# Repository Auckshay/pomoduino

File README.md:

# Pomoduino (An Arduino UNO shield)

A little DIY Pomodoro timer to keep you focused and away from pesky distractions.

(3D model)

## How it works
To use the pomoduino, in front of a distracting object, making sure that the sensor is unobscured, and a clear path in front of it to detect movement. Then set the timer length and break length, and start it.
## Why I made this
Every single time I sat down, planning to work on something, I always found myself instinctively reaching for my phone. I knew this was an issue, and I, of course, tried to set screen time limits and pomodoro timers to keep me locked in. Still, I found myself either disabling them or just finding some other convoluted workaround subconsciously. But I knew that I've always been a person who obeys physical obstruction. That's when I got the idea of creating a device that aided me in focus with a pomoduro timer, but also physically reminded me to focus up.
## Design Images
### Schematic Design

### PCB Design

## B.O.M.

|Name                                                                                                                  |Purpose                                   |Qty|Cost (USD)|LINK                                                                                  |Distributor|
|----------------------------------------------------------------------------------------------------------------------|------------------------------------------|---|----------|--------------------------------------------------------------------------------------|-----------|
|Monochrome_OLED_128X64_.96_I2C-1pc                                                                                    |Display Count Down, Distraction Notif, ect|1  |6.99$     |https://a.co/d/0dFfSqWY                                                               |Amazon     |
|2.54mm Pin Header, Male Straight Single Row Header Pin 180 Degree Connector,1x2 1x3 1x4 1x5 1x6 1x7 1x8 1x9 1x10 1x12 |For mounting to Arduino UNO               |1  |11.99$    |https://a.co/d/0gofrzR4                                                               |Amazon     |
|Passive Buzzer-5pc                                                                                                    |Auditory Output                           |1  |1.18$     |https://www.aliexpress.us/item/3256806074013807.html                                  |AliExpress |
|220Ω Resistor-10pc                                                                                                    |Current limiting                          |1  |1.46$     |https://www.aliexpress.us/item/3256802927431747.html                                  |AliExpress |
|Colorful Push Button-12mm-15pc                                                                                        |Human Interaction                         |1  |5.95$     |https://www.adafruit.com/product/1010                                                 |Adafruit   |
|HC-SR04-1pc                                                                                                           |Distance measurement                      |1  |6.17$     |https://www.aliexpress.us/item/3256810043926609.html?gatewayAdapt=glo2usa             |AliExpress |
|PCB-5pc                                                                                                               |For mounting and connecting all components|1  |5.00$     |https://www.pcbway.com/orderonline.aspx?outsideid=d9d46809-3d4a-4ff4-aac3-b91ac39b3b48|PCBWAY     |

### External Hardware Required
- 1x Arduino UNO (R3 or R4) – The host board.
- 1x USB-C Cable or USB-B, depending on the Arduino version.

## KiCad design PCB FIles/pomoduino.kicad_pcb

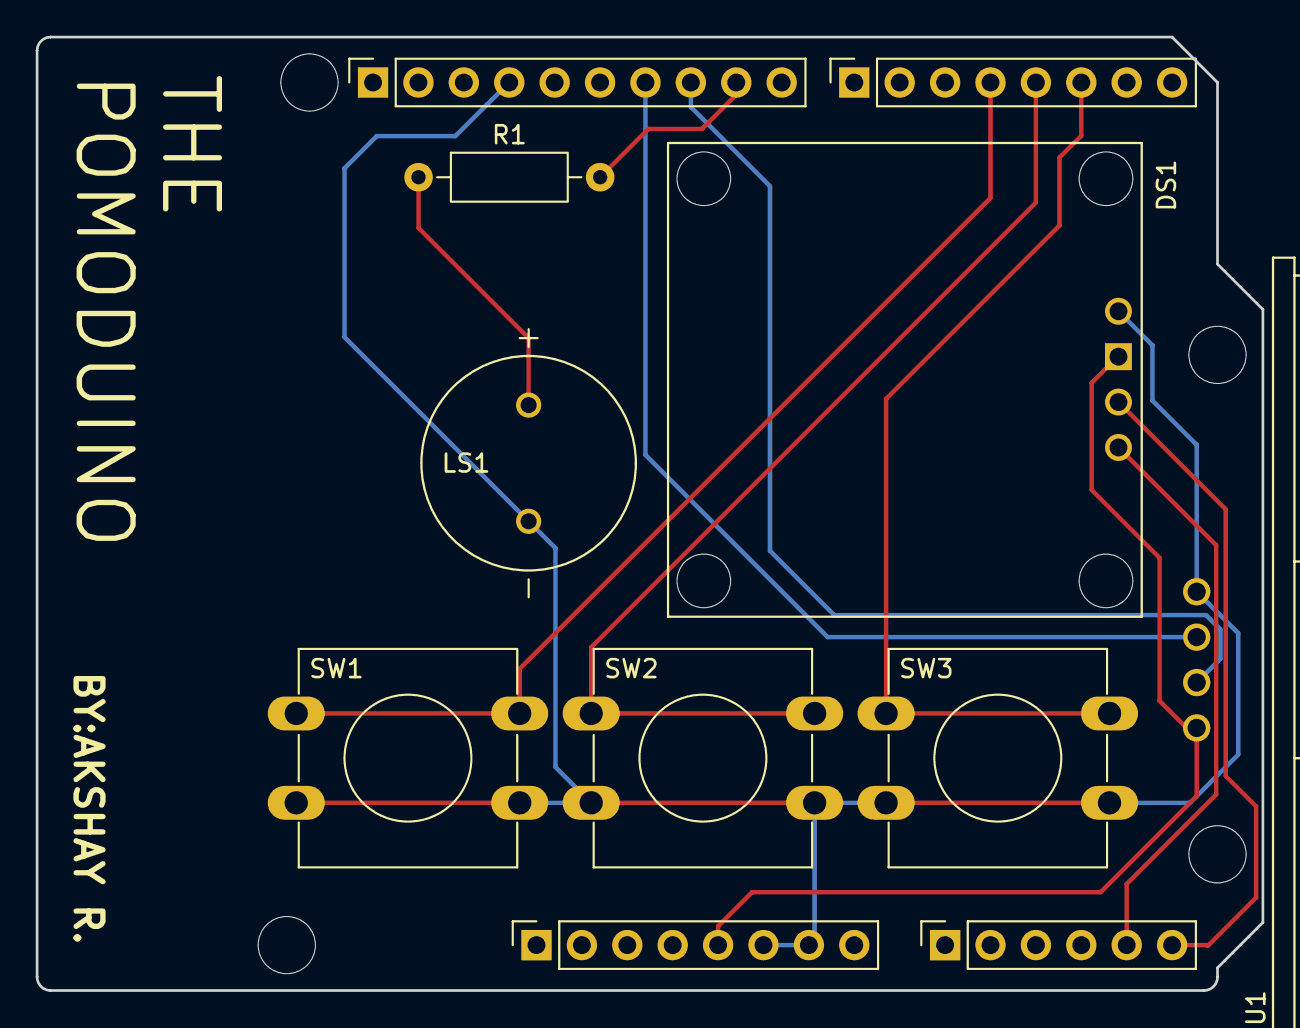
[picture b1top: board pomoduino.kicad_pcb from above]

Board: 2 copper layers, 68.6 x 53.3 mm, 15 parts (0 on the bottom side), 11 nets.

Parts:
DS1: OLED_128X64_.96_I2C; LCD_OLED_128X64_1.3_I2C
J1: Power; PinSocket_1x08_P2.54mm_Vertical
J2: Digital/PWM; PinSocket_1x10_P2.54mm_Vertical
J3: Analog; PinSocket_1x06_P2.54mm_Vertical
J4: Digital/PWM; PinSocket_1x08_P2.54mm_Vertical
LS1: Speaker; XDCR_KSSG1201-16
MH1, MH2, MH3, MH4: MountingHole_3.2mm
R1: R_220Ω; R_Axial_DIN0207_L6.3mm_D2.5mm_P10.16mm_Horizontal
SW1: SW (GREEN); SW_PUSH-12mm
SW2: SW (YELLOW); SW_PUSH-12mm
SW3: SW (RED); SW_PUSH-12mm
U1: HC-SR04; XCVR_HC-SR04

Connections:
+5V: DS1.1 (VDD), J1.5, U1.1 (VCC)
/2: J4.6, SW3.1
/4: J4.4, SW1.1
/*3: J4.5, SW2.1
/*9: J2.9, R1.2
/*10: J2.8, U1.2 (TRIG)
/*11: J2.7, U1.3 (ECHO)
/SCL/A5: DS1.3 (SCK), J3.6
/SDA/A4: DS1.4 (SDA), J3.5
GND: DS1.2 (GND), J1.6, J1.7, J2.4, LS1.N, SW1.2, SW2.2, SW3.2, U1.4 (GND)
unnamed: LS1.P, R1.1

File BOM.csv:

Reference,Name,Purpose,Qty,Cost (USD),LINK
DS1,Monochrome_OLED_128X64_.96_I2C,"Display Count Down, Distraction Notif, ect",1,6.99,https://a.co/d/0dFfSqWY
"J1,J2",Male Pin Header-1x8-P2.54mm,For mounting to Arduino UNO,2,11.99,https://a.co/d/0gofrzR4 (Bulk order applicable for other projects) 
J3,Male Pin Header-1x6-P2.54mm,For mounting to Arduino UNO,1,N/A,bundled above
J4,Male Pin Header-1x10-P2.54mm,For mounting to Arduino UNO,1,N/A,bundled above
LS1,Passive Buzzer,Auditory input,1,Owned,N/A
R1,220Ω Resistor,Current limiting,1,Owned,N/A
"SW1,SW2,SW3",Push Button-12mm,Human Interaction,3,Owned,N/A
U1,HC-SR04,Distance measurement,1,Owned,N/A
,PCB,For mounting and connecting all components,1,(Global Direct Shipping) 11.31,https://www.pcbway.com/orderonline.aspx?outsideid=d9d46809-3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

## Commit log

2026-04-26 Update copyright year and owner in LICENSE file
2026-04-26 Update project title in README
2026-06-12 Enhance README with project information and images
    Expanded README to include project details, usage instructions, design images, and bill of materials.
2026-06-12 Added SRC files
2026-06-12 Fix grammar and punctuation in README.md
    Corrected grammar and punctuation in the README.
2026-06-12 Add comment for board specification in platformio.ini
    Added a comment to specify the board used by the developer.
2026-06-12 Firmware uplaod
2026-06-12 Update README with external hardware requirements
    Added external hardware requirements for Arduino setup.
2026-06-12 Renamed Folder
2026-06-13 PCB files upload
2026-06-13 Fix BOM entry for OLED display reference
2026-06-13 Revise BOM table format and update component details
2026-06-13 BOM upload
2026-06-13 Update BOM table to include distributor details
    Added distributor information to the BOM table in README.
2026-06-13 Revise B.O.M. with updated components and links
    Updated the bill of materials (B.O.M.) section with new component details and links.
2026-06-13 Edited BOM
2026-06-18 PCB files + step files associated
2026-06-18 Delete shayfinder directory
    uploaded to wrong repo
